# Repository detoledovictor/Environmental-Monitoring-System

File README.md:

# Environmental Monitoring System

This project is a real-time environmental and motion monitoring system based on the ESP32 with FreeRTOS. It features a TFT display, Wi-Fi connectivity, temperature and acceleration sensing, and visual status indication via an RGB LED.

## 🔧 Features

- 📶 Wi-Fi connection with automatic reconnection
- 🌐 NTP time synchronization (UTC-3)
- 🌡️ Temperature reading (BMP280)
- 🧭 3-axis acceleration monitoring (MMA8452Q)
- 🖥️ 240x240 TFT display with 7-segment styled digital clock
- 🎨 Graphical display of data with FreeRTOS-controlled tasks
- 🔴🟡🟢 RGB LED status indicator using FastLED

## ⚙️ Architecture

- Multitasking with FreeRTOS (`TaskWiFiConnect`, `TaskDateTime`, `TaskReadSensors`, etc.)
- Inter-task communication via `QueueHandle_t`
- Display rendering protected by `SemaphoreHandle_t`

## 📚 Dependencies

- [TFT_eSPI](https://github.com/Bodmer/TFT_eSPI)
- [FastLED](https://github.com/FastLED/FastLED)
- [Adafruit BMP280 Library](https://github.com/adafruit/Adafruit_BMP280_Library)
- [RoboCore MMA8452Q](https://github.com/RoboCore/MMA8452Q)
- `WiFi.h`, `NTPClient.h`, `Wire.h`, `SPI.h`

## 📦 Hardware

- ESP32 Dev Module
- 1x TFT 240x240 display (SPI)
- 1x BMP280 sensor (I2C)
- 1x MMA8452Q accelerometer (I2C)
- 1x RGB LED (Neopixel - GPIO 19)

## 📸 Preview

> [Add image or GIF here of the display in action]

## 🛠️ Setup

1. Install libraries listed above via Library Manager or git.
2. Connect peripherals according to pin mapping.
3. Set your Wi-Fi credentials in the code (`ssid`, `password`).
4. Upload using Arduino IDE or PlatformIO.

## 📄 License

MIT License

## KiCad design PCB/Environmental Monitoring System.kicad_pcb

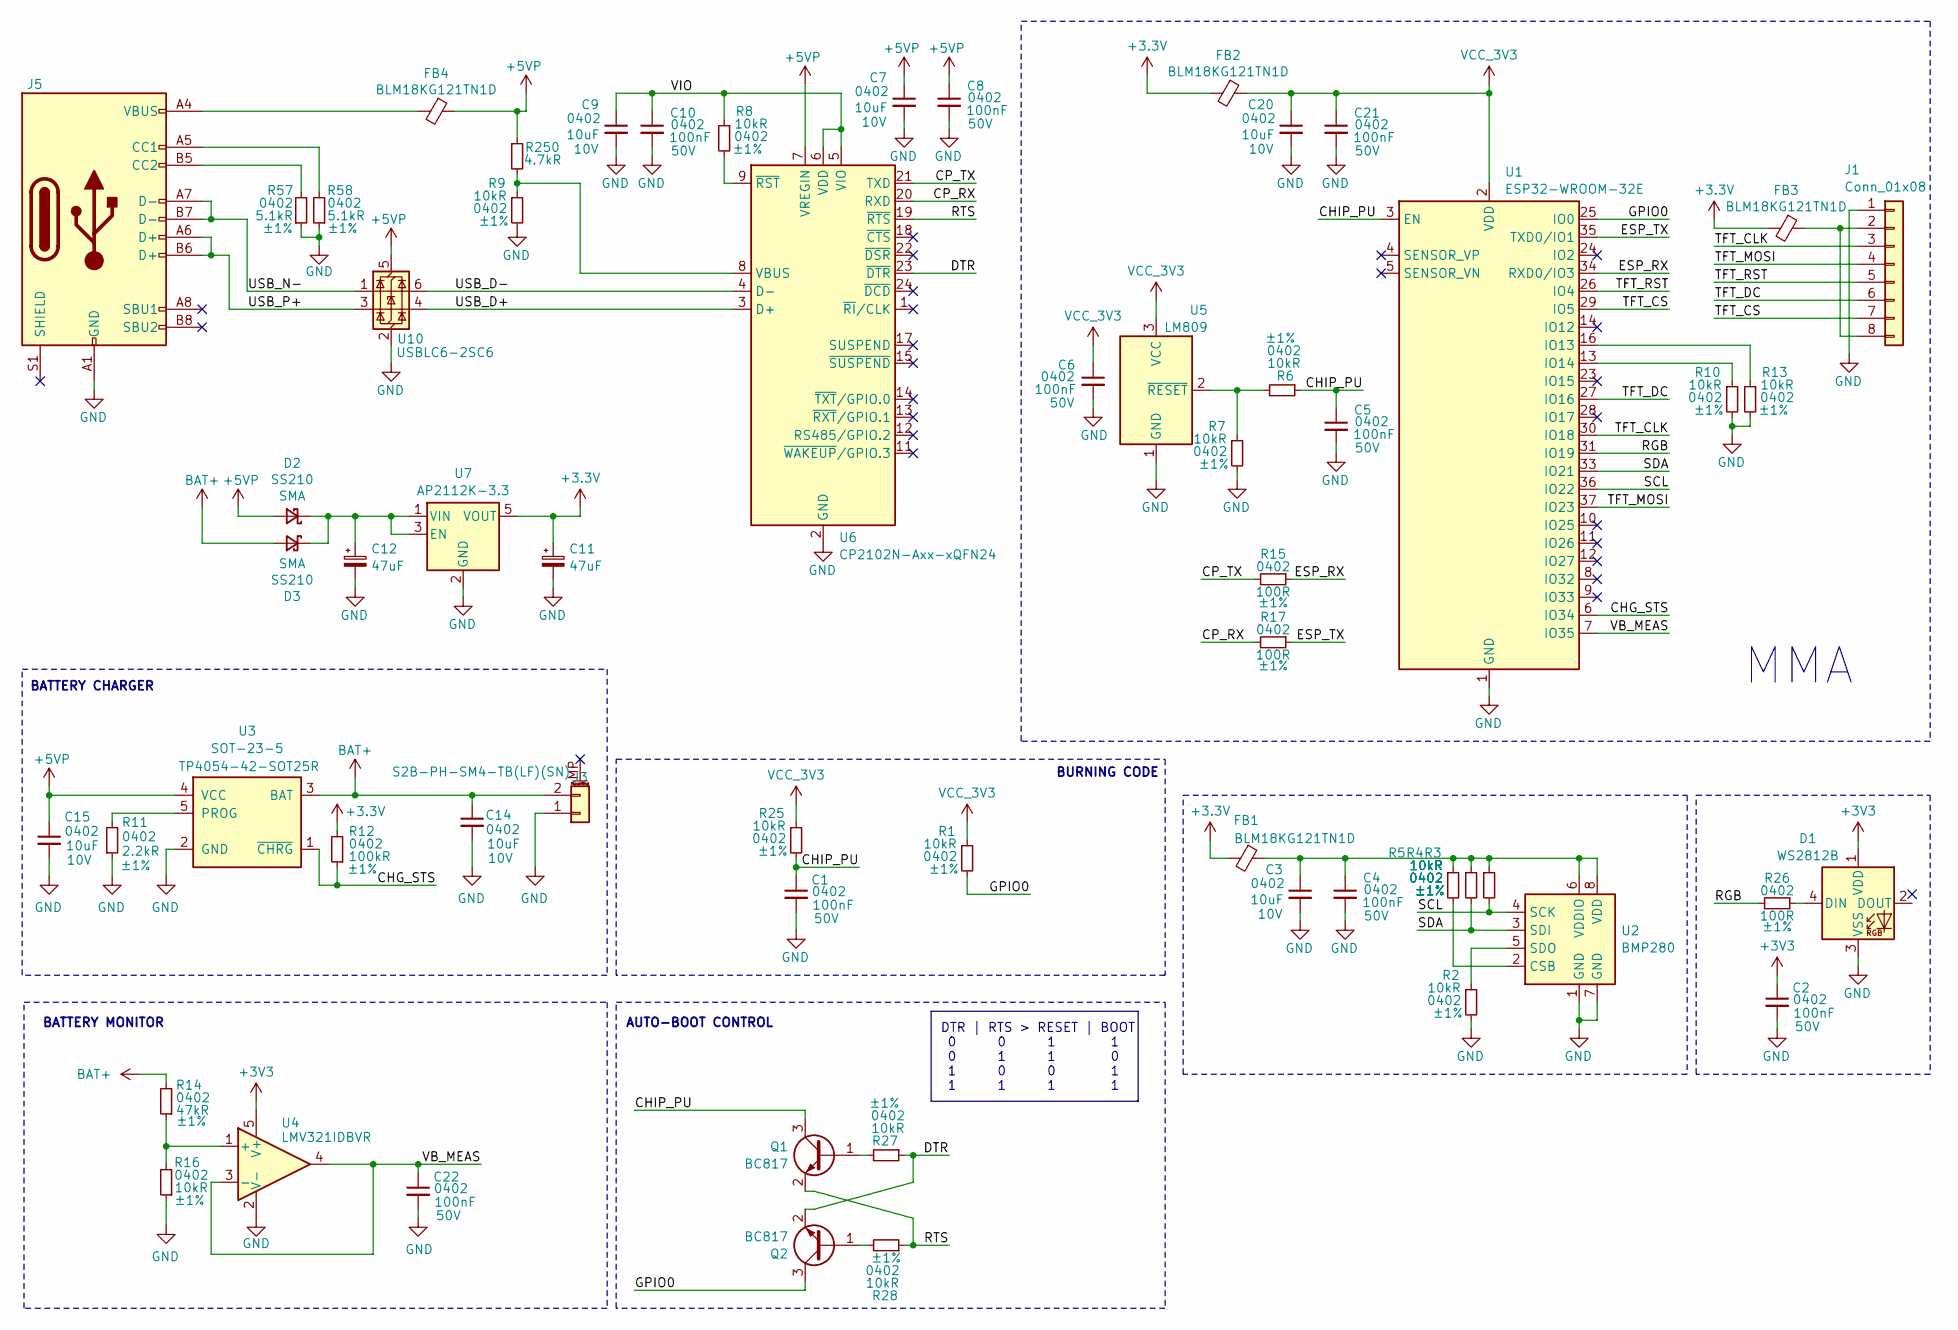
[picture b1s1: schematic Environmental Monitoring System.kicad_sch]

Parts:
C1, C2, C4, C5, C6, C8, C10, C21, C22: 100nF; C_0402_1005Metric; Voltage 50V; Part CL05B104KB5NNNC; LCSC C960916
C3, C7, C9, C14, C15, C20: 10uF; C_0402_1005Metric; Voltage 10V; Part CL05A106MP5NUNC; LCSC C315248
C11, C12: 47uF; CP_EIA-3216-18_Kemet-A
D1: WS2812B; LED_WS2812B-Mini_PLCC4_3.5x3.5mm
D2, D3: SS210; D_SMA; Voltage 100V; Part SS210; LCSC C14996
FB1, FB2, FB3, FB4: BLM18KG121TN1D; L_0603_1608Metric; Part BLM18KG121TN1D; LCSC C85831
J1: Conn_01x08; PinHeader_1x08_P2.54mm_Vertical
J3: S2B-PH-SM4-TB(LF)(SN); JST_PH_B2B-PH-K_1x02_P2.00mm_Vertical; Part S2B-PH-SM4-TB(LF)(SN); LCSC C295747
J5: USB_C_Receptacle_USB2.0_16P; USB_C_Receptacle_GCT_USB4105-xx-A_16P_TopMnt_Horizontal; Part TYPE-C 16PIN 2MD(073); LCSC C2765186
Q1, Q2: BC817; SOT-23
R1, R2, R3, R4, R5, R6, R7, R8, R9, R10, R13, R16, R25, R27, R28: 10KR; R_0402_1005Metric; Tolerance ±1%; Part 0402WGF1002TCE; LCSC C25744
R11: 2.2KR; R_0402_1005Metric; Tolerance ±1%; Part 0402WGF2201TCE; LCSC C25879
R12: 100KR; R_0402_1005Metric; Tolerance ±1%; Part 0402WGF1003TCE; LCSC C25741
R14: 47KR; R_0402_1005Metric; Tolerance ±1%; Part 0402WGF4702TCE; LCSC C25792
R15, R17, R26: 100R; R_0402_1005Metric; Tolerance ±1%; Part 0402WGF1000TCE; LCSC C25076
R57, R58: 5.1KR; R_0402_1005Metric; Tolerance ±1%; Part 0402WGF5101TCE; LCSC C25905
R250: 4.7kR; R_0402_1005Metric; Tolerance ±1%; Part 0402WGF4701TCE; LCSC C25900
U1: ESP32-WROOM-32E; ESP32-WROOM-32D
U2: BMP280; Bosch_LGA-8_2x2.5mm_P0.65mm_ClockwisePinNumbering
U3: TP4054; SOT-23-5; Part TP4054-42-SOT25R; LCSC C32574
U4: LMV321; SOT-23-5; Part LMV321IDBVR; LCSC C3014306
U5: LM809; SOT-23
U6: CP2102N-Axx-xQFN24; QFN-24-1EP_4x4mm_P0.5mm_EP2.6x2.6mm; Part CP2102N-A02-GQFN24R; LCSC C969151
U7: AP2112K-3.3; SOT-23-5
U10: USBLC6-2SC6; SOT-23-6; Part USBLC6-2SC6; LCSC C7519

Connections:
+3.3V: C11.1, FB1.2, FB2.2, FB3.2, R12.2, U7.5 (VOUT)
+3V3: C2.1, D1.1 (VDD), U4.5 (V+)
+5VP: C7.1, C8.1, C15.1, D2.2 (A), FB4.1, R250.1, U3.4 (VCC), U6.7 (VREGIN), U10.5 (VBUS)
/CHG_STS: R12.1, U1.6 (IO34), U3.1 (~CHRG)
/CHIP_PU: C1.1, C5.1, Q1.3 (C), R6.1, R25.2, U1.3 (EN)
/CP_RX: R17.2, U6.20 (RXD)
/CP_TX: R15.2, U6.21 (TXD)
/DTR: Q2.2 (E), R27.1, U6.23 (~DTR)
/ESP_RX: R15.1, U1.34 (RXD0/IO3)
/ESP_TX: R17.1, U1.35 (TXD0/IO1)
/GPIO0: Q2.3 (C), R1.2, U1.25 (IO0)
/RGB: R26.2, U1.31 (IO19)
/RTS: Q1.2 (E), R28.1, U6.19 (~RTS)
/SCL: R3.2, U1.36 (IO22), U2.4 (SCK)
/SDA: R4.2, U1.33 (IO21), U2.3 (SDI)
/TFT_CLK: J1.3, U1.30 (IO18)
/TFT_CS: J1.7, U1.29 (IO5)
/TFT_DC: J1.6, U1.27 (IO16)
/TFT_MOSI: J1.4, U1.37 (IO23)
/TFT_RST: J1.5, U1.26 (IO4)
/USB_D+: U6.3 (D+), U10.4 (I/O2)
/USB_D-: U6.4 (D-), U10.6 (I/O1)
/USB_N-: J5.A7 (D-), J5.B7 (D-), U10.1 (I/O1)
/USB_P+: J5.A6 (D+), J5.B6 (D+), U10.3 (I/O2)
/VB_MEAS: C22.1, U1.7 (IO35), U4.3 (-), U4.4
/VIO: C9.1, C10.1, R8.1, U6.5 (VIO), U6.6 (VDD)
BAT+: C14.1, D3.2 (A), J3.2, R14.2, U3.3 (BAT)
GND: C1.2, C2.2, C3.2, C4.2, C5.2, C6.2, C7.2, C8.2, C9.2, C10.2, C11.2, C12.2, C14.2, C15.2, C20.2, C21.2, C22.2, D1.3 (VSS), J1.1, J3.1, J5.A1 (GND), J5.A12 (GND), J5.B1 (GND), J5.B12 (GND), R2.2, R7.2, R9.2, R10.2, R11.1, R13.2, R16.1, R57.1, R58.1, U1.1 (GND), U1.15 (GND), U1.38 (GND), U1.39 (GND), U2.1 (GND), U2.7 (GND), U3.2 (GND), U4.2 (V-), U5.1 (GND), U6.2 (GND), U6.25 (GND), U7.2 (GND), U10.2 (GND)
unnamed: D1.4 (DIN), R26.1
unnamed: C12.1, D2.1 (K), D3.1 (K), U7.1 (VIN), U7.3 (EN)
unnamed: FB4.2, J5.A4 (VBUS), J5.A9 (VBUS), J5.B4 (VBUS), J5.B9 (VBUS)
unnamed: FB3.1, J1.2, J1.8
unnamed: J5.A5 (CC1), R58.2
unnamed: J5.B5 (CC2), R57.2
unnamed: Q1.1 (B), R27.2
unnamed: Q2.1 (B), R28.2
unnamed: R13.1, U1.16 (IO13)
unnamed: R10.1, U1.13 (IO14)
unnamed: R5.2, U2.2 (CSB)
unnamed: R2.1, U2.5 (SDO)
unnamed: C3.1, C4.1, FB1.1, R3.1, R4.1, R5.1, U2.6 (VDDIO), U2.8 (VDD)
unnamed: R11.2, U3.5 (PROG)
unnamed: R14.1, R16.2, U4.1 (+)
unnamed: R6.2, R7.1, U5.2 (~RESET)
unnamed: R9.1, R250.2, U6.8 (VBUS)
unnamed: R8.2, U6.9 (~RST)
VCC_3V3: C6.1, C20.1, C21.1, FB2.1, R1.1, R25.1, U1.2 (VDD), U5.3 (VCC)

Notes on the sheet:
DTR | RTS > RESET | BOOT 0 0 1 1 0 1 1 0 1 0 0 1 1 1 1 1
BATTERY CHARGER
AUTO-BOOT CONTROL
BURNING CODE
MMA
BATTERY MONITOR

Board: 2 copper layers, 61 parts (4 on the bottom side), 47 nets, no tracks yet.
